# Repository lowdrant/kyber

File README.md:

# kyber
The toy lightsaber I always wanted as a kid.

## Status
* KyberBoard Rev 1 sent out for fabrication.
* Found Luke Skywalker lightsaber CAD for 3D printing by [CaseStudyno8](https://www.thingiverse.com/thing:1263192/files).
* Circuit design complete and subcircuit interfaces frozen.
* Subcircuits passed breadboard feasibility tests.
* First pass on firmware architecture complete.

## Goals
- Build a lightsaber that extends/retracts, lights up, and makes sound
- Demonstrate "full-stack" electronics engineering skills + some mechanical design
- Stay sane for the rest of the pandemic (everyone needs a hobby)
- Maybe have a Luke Skywalker costume by Halloween 2021?

## [fw](fw/)
Written for the [STM32L051K8T6](hw/KyberBoard/symbol-datasheets/stm32l051t8.pdf) microcontroller. Code should work on any STM32 micrcontroller, and most interfaces are abstracted into header files.

TODO: state diagram

### Configuring STM32CubeIde
Edit project settings to include the multi-project libraries and make the compiler optimize for size. TODO: change saber-libs to holocron-libs

## [hw](hw/)
A mildly overdesigned PCB to allow flexibility in mechanical design. Designed for test, assembly, and reconfigurability.

### Component Selection Rules
Keep It Simple, Stupid. Stick to driving circuits that have readily available and easily solderable components. If necessary, target components that have in-stock evaluation boards and take the scrap.

### Current (A) Budget
|Component  |Amperage  |Reasoning                        |
|-----------|----------|---------------------------------|
|motor      |10A       |stall current of on-hand dc motor|
|solenoid   |1A        |12 V/13 Ohms rounded up          |
|3V3 bus    |1A        |typical LDO rating               |
|waste      |0.5A      |safety factor                    |
|-----------|----------|---------------------------------|
|total      |12.5A     |                                 |

### Voltage Loss Budget
Mostly concerned with battery protection I<sup>2</sup>R losses. Target < 0.5V peak drop (instinctive spec, not computed)

Major concerns are
- falling below the solenoid turn-on voltage, although I haven't _really_ settled on a solenoid
- throwing off motor control

Current resolution: use ST's [VNHD7008AY eval board example design](reference-manuals/en-vnhd7008ay.pdf). It seems to work fairly well

### Subcircuits
#### Reverse Polarity Protection
Use the built-in protection of the hbridge. Need to characterise I<sup>2</sup>R losses. This will help prevent the Big Dumb<sup>TM</sup> since I plan to use terminal blocks for my main connector.
#### Low-Voltage Shutoff
Grocery store batteries can't drive the actuators, so I'm looking at using a LiPo. This simple Zener-NMOS-PMOS circuit I designed for a student club will should prevent battery over-discharge.

When the voltage is above Vthresh, the Zener conducts, so the NMOS conducts, which makes the PMOS conduct.
#### 3V3 Bus
LDO; I do not want to deal with buck converters. I am not being paid for this design.
#### Accelerometer/Gyro
For that sweet, sweet _zwoom_. Use I2C/SPI to make routing a little easier. I have a still-in-stock breakout board for the no-longer-produced [MMA84252QT](https://www.digikey.com/catalog/en/partgroup/mma8452q/11242).
#### Motor Current Sensing
I may use torque control to retract the saber. Currently planning to extend it with a spring, so the "retracted torque" is theoretically better characterized than the "retracted position".
#### HBridge
I found a high-current hbridge IC that does not require complementary PWM (thank you ST). I have limited PWM capabilities due to only low-power ST micros being in stock.
#### Actuators
Low-side switches that do not require inrush-limiting resistors to reduce component count. The [SSM3K337R,LF](https://www.digikey.com/en/products/detail/toshiba-semiconductor-and-storage/SSM3K337R-LF/5056502?s=N4IgTCBcDaIMpwLIGYDSzkHYBKIC6AvkA) stays well under the maximum drive current and well-preserves a 20kHz square wave.

### Non-electrical considerations
- Cost: 4 layers. 2-sided board gives me the needed density, and routing isn't that awful
- I'm not sure I want to hand-solder QFN packages
- Size: Maximize density to maximize mechanical design flexibility.
- Power budget: Meh, I can increase resistances after fab if it's a battery killer

## [cad](cad/)
Found a Luke Skywalker lightsaber CAD for 3D printing by [CaseStudyno8](https://www.thingiverse.com/thing:1263192/files). Was also pointed to Disney's [new lightsaber](https://mashable.com/article/real-lightsaber-star-wars-hotel-disney-world/), which shows some novel mechanical design for retraction. Although I would prefer to be able to fence with my design, the tape measure strategy does show promise.

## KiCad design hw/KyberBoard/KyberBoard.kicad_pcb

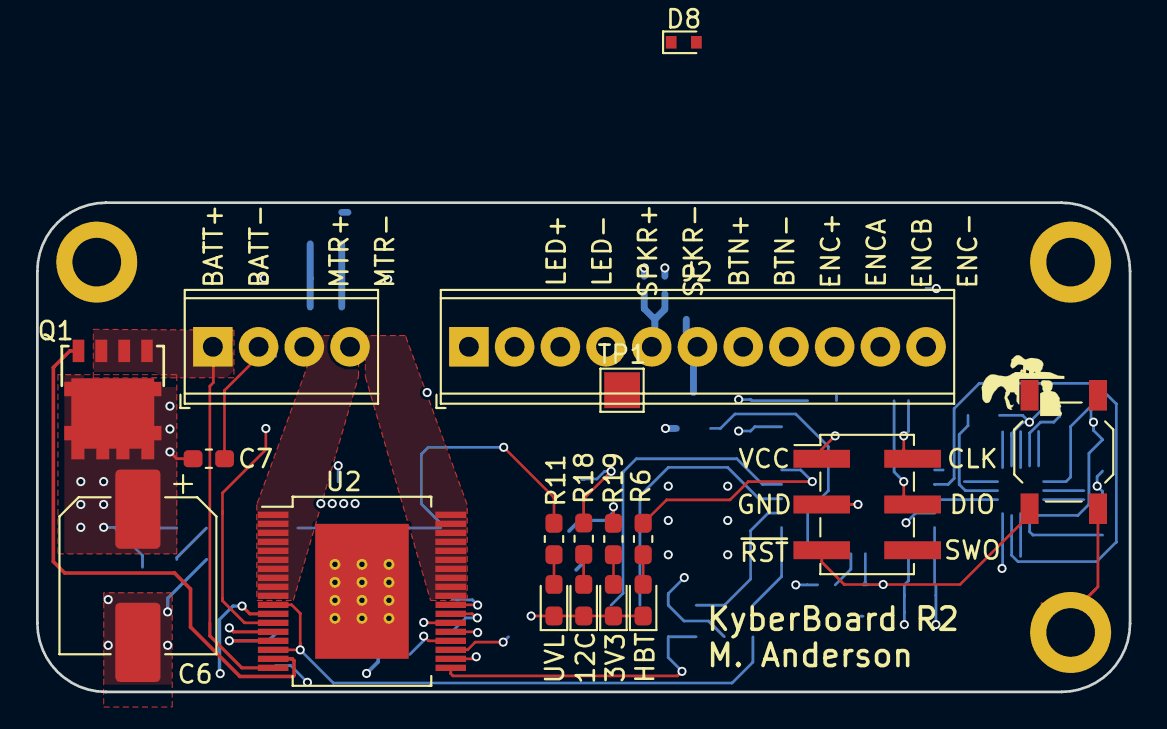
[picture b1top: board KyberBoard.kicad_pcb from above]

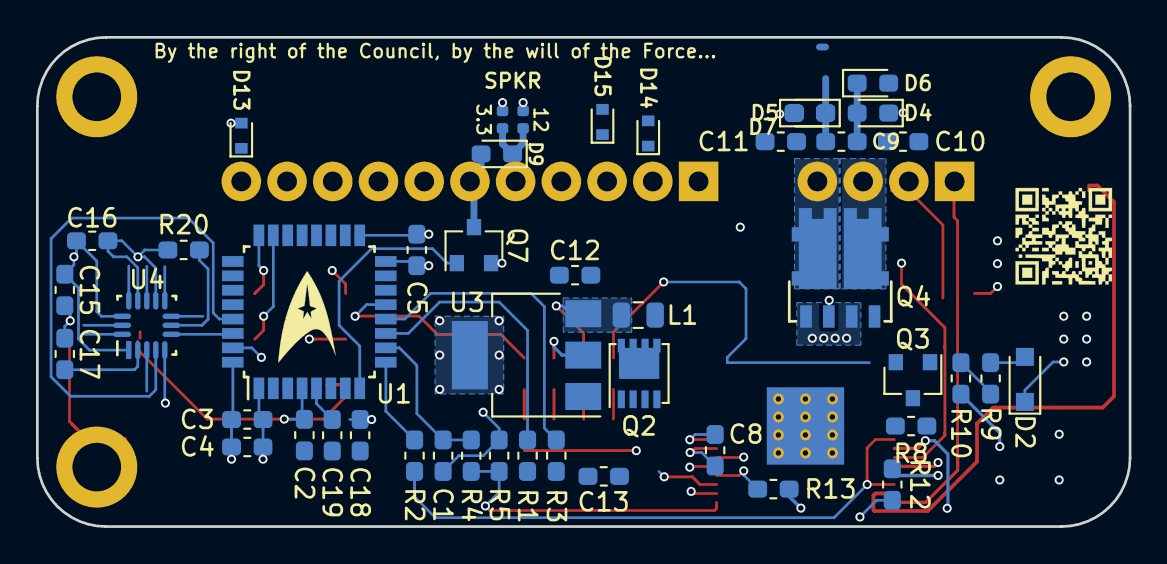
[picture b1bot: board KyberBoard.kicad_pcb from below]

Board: 4 copper layers, 60.7 x 27.2 mm, 67 parts (46 on the bottom side), 44 nets.

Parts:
C1: 33n; C_0603_1608Metric_Pad1.05x0.95mm_HandSolder
C2, C4, C5, C7, C8, C15, C17, C18: 100n; C_0603_1608Metric_Pad1.05x0.95mm_HandSolder
C3, C12: 10u; C_0603_1608Metric_Pad1.05x0.95mm_HandSolder
C6: 200u; CP_Elec_8x10.5
C9, C10, C11: 10n; C_0603_1608Metric_Pad1.05x0.95mm_HandSolder
C13: 22u; C_0603_1608Metric_Pad1.05x0.95mm_HandSolder
C16: 4u7; C_0603_1608Metric_Pad1.05x0.95mm_HandSolder
C19: 1u; C_0603_1608Metric_Pad1.05x0.95mm_HandSolder
D1: 150060VS75020; LED_0603_1608Metric_Pad1.05x0.95mm_HandSolder
D2: BZT52C8V2S-7-F; D_SOD-323_HandSoldering
D3: 150060RS75020; LED_0603_1608Metric_Pad1.05x0.95mm_HandSolder
D4, D5, D6, D7, D9: SDM2U30CSP-7; D_0603_1608Metric_Pad1.05x0.95mm_HandSolder
D8, D13, D14, D15: BZT585B3V6T; D_SOD-523
D10, D11: 150060AS75000; LED_0603_1608Metric_Pad1.05x0.95mm_HandSolder
H1, H3, H4: MountingHole_Pad; MountingHole_2.7mm_M2.5_ISO7380_Pad
J1: Screw_Terminal_01x04; TerminalBlock_Phoenix_MPT-0,5-4-2.54_1x04_P2.54mm_Horizontal
J2: Screw_Terminal_01x11; TerminalBlock_Phoenix_MPT-0,5-11-2.54_1x11_P2.54mm_Horizont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
J4: 15910060; PinHeader_2x03_P2.54mm_Vertical_SMD
L1: CIGT201210UHR47MNE; C_0805_2012Metric
Q1: STL120N4F6AG
Q2: SIS413DN-T1-GE3; Vishay_PowerPAK_1212-8_Single
Q3: SSM3K337R; SOT-23
Q4: STL76DN4LF7AG
Q7: SSM3K337R,LF; SOT-23
R1, R2, R3, R6, R8, R10, R19, R20: 1k; R_0603_1608Metric_Pad1.05x0.95mm_HandSolder
R4, R11, R12, R13, R18: 10k; R_0603_1608Metric_Pad1.05x0.95mm_HandSolder
R5: 1k5; R_0603_1608Metric_Pad1.05x0.95mm_HandSolder
R9: 0; R_0603_1608Metric_Pad1.05x0.95mm_HandSolder
R16, R17: 0; R_0402_1005Metric
SW1: TL3342F160QG/TR; SW_SPST_TL3342
TP1: TestPoint; TestPoint_Pad_2.0x2.0mm
U1: STM32L051K8T6; LQFP-32_7x7mm_P0.8mm
U2: VNHD7008AY; ST_PowerSSO-36_SlugDown_ThermalVias
U3: AZ1117IH-3.3TRG1; SOT-223-3_TabPin2
U4: MMA8452QT; MMA8452Q

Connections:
+3V3: C3.1, C4.1, C5.1, C13.1, C15.2, C16.2, C18.1, C19.1, J2.1, J2.7, J2.10, J4.1, R17.1, R19.1, U1.1, U1.5, U1.17, U2.12, U3.2, U4.1, U4.14
+12C: C12.2, L1.1, R18.1, U3.3
+12V: L1.2, Q2.5, R16.2
/BATT+: J1.1, Q1.1, Q1.2, Q1.3, U2.18
/BTN: D13.1, J2.11, U1.19
/ENC_A: D14.1, J2.2, U1.28
/ENC_B: D15.1, J2.3, U1.27
/LED_TX: D8.1, J2.8
/MOT+: C9.2, C10.1, D4.2, D6.1, J1.3, Q4.5/6, U2.1, U2.2, U2.3, U2.4, U2.5, U2.6, U2.7, U2.8, U2.9, U2.10
/MOT-: C9.1, C11.1, D5.2, D7.1, J1.4, Q4.7/8, U2.27, U2.28, U2.29, U2.30, U2.31, U2.32, U2.33, U2.34, U2.35, U2.36
/SPKR+: D9.1, J2.5, R16.1, R17.2
/SPKR-: D9.2, J2.6, Q7.3
/V_UNSAFE: C6.1, C7.1, D2.1, D4.1, D5.1, Q1.5, Q2.1, Q2.2, Q2.3, R8.1, U2.37
/acc/SCL: U1.29, U4.4
/acc/SDA: U1.30, U4.6
/actuators/PWM_SPKR: Q7.1, TP1.1, U1.8
/hbridge/INA: R2.2, U2.11, U2.16
/hbridge/INB: R3.2, U2.21
/hbridge/PWM_MTR: R1.2, U2.20
/hbridge/imtr: R4.2, R5.1, U2.19
/micro/ADC_imtr: C1.1, R4.1, U1.10
/micro/INA_MCU: R2.1, U1.9
/micro/INB_MCU: R3.1, U1.12
/micro/LED_HBEAT: R6.2, U1.13
/micro/NRST: C2.1, J4.5, SW1.1, U1.4
/micro/PWM_MTR_MCU: R1.1, U1.11
/micro/SWCLK: J4.2, U1.24
/micro/SWDIO: J4.4, U1.23
GND: C1.2, C2.2, C3.2, C4.2, C5.2, C6.2, C7.2, C8.2, C10.2, C11.2, C12.1, C13.2, C15.1, C16.1, C17.1, C18.2, C19.2, D1.1, D3.1, D6.2, D7.2, D8.2, D10.1, D11.1, D13.2, D14.2, D15.2, H1.1, H3.1, H4.1, J1.2, J2.4, J2.9, J4.3, Q3.2, Q4.1, Q4.3, Q7.2, R5.2, R10.1, R12.2, R13.2, R20.2, SW1.2, U1.16, U1.31, U1.32, U2.14, U2.23, U2.26, U3.1, U4.5, U4.10, U4.12
unnamed: C8.1, U2.25
unnamed: C17.2, U4.2
unnamed: D1.2, R6.1
unnamed: D2.2, R9.2
unnamed: D3.2, R11.2
unnamed: D10.2, R18.2
unnamed: D11.2, R19.2
unnamed: Q1.4, U2.17
unnamed: Q2.4, Q3.3, R8.2, R11.1
unnamed: Q3.1, R9.1, R10.2
unnamed: Q4.2, U2.24
unnamed: Q4.4, U2.13
unnamed: R12.1, U2.15
unnamed: R13.1, U2.22
unnamed: R20.1, U4.7

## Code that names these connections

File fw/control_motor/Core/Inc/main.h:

/* USER CODE BEGIN Header */
/**
  ******************************************************************************
  * @file           : main.h
  * @brief          : Header for main.c file.
  *                   This file contains the common defines of the application.
  ******************************************************************************
  * @attention
  *
  * <h2><center>&copy; Copyright (c) 2021 STMicroelectronics.
  * All rights reserved.</center></h2>
  *
  * This software component is licensed by ST under BSD 3-Clause license,
  * the "License"; You may not use this file except in compliance with the
  * License. You may obtain a copy of the License at:
  *                        opensource.org/licenses/BSD-3-Clause
  *
  ******************************************************************************
  */
/* USER CODE END Header */

/* Define to prevent recursive inclusion -------------------------------------*/
#ifndef __MAIN_H
#define __MAIN_H

#ifdef __cplusplus
extern "C" {
#endif

/* Includes ------------------------------------------------------------------*/
#include "stm32l0xx_hal.h"

/* Private includes ----------------------------------------------------------*/
/* USER CODE BEGIN Includes */
/* USER CODE END Includes */

/* Exported types ------------------------------------------------------------*/
/* USER CODE BEGIN ET */

/* USER CODE END ET */

/* Exported constants --------------------------------------------------------*/
/* USER CODE BEGIN EC */
#define T_HBEAT (float) 0.5  // LED Heartbeat Period
#define T_MTR (float) 0.1    // mot stuff
/* USER CODE END EC */

/* Exported macro ------------------------------------------------------------*/
/* USER CODE BEGIN EM */

/* USER CODE END EM */

void HAL_TIM_MspPostInit(TIM_HandleTypeDef *htim);

/* Exported functions prototypes ---------------------------------------------*/
void Error_Handler(void);

/* USER CODE BEGIN EFP */

/* USER CODE END EFP */

/* Private defines -----------------------------------------------------------*/
#define SIG_LED_Pin GPIO_PIN_14
#define SIG_LED_GPIO_Port GPIOC
#define SIG_SOL_Pin GPIO_PIN_15
#define SIG_SOL_GPIO_Port GPIOC
#define PWM_SPKR_Pin GPIO_PIN_0
#define PWM_SPKR_GPIO_Port GPIOA
#define PWM_MTR_Pin GPIO_PIN_1
#define PWM_MTR_GPIO_Port GPIOA
#define INA_Pin GPIO_PIN_2
#define INA_GPIO_Port GPIOA
#define INB_Pin GPIO_PIN_3
#define INB_GPIO_Port GPIOA
#define ADC_imtr_Pin GPIO_PIN_4
#define ADC_imtr_GPIO_Port GPIOA
#define LED_HBEAT_Pin GPIO_PIN_5
#define LED_HBEAT_GPIO_Port GPIOA
#define ENC_B_Pin GPIO_PIN_6
#define ENC_B_GPIO_Port GPIOA
#define ENC_A_Pin GPIO_PIN_7
#define ENC_A_GPIO_Port GPIOA
#define BTN_Pin GPIO_PIN_1
#define BTN_GPIO_Port GPIOB
#define BTN_EXTI_IRQn EXTI0_1_IRQn
/* USER CODE BEGIN Private defines */

/* USER CODE END Private defines */

#ifdef __cplusplus
}
#endif

#endif /* __MAIN_H */

/************************ (C) COPYRIGHT STMicroelectronics *****END OF FILE****/

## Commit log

2021-04-07 firmware setup & gitignore
2021-04-07 Ticks-based scheduler & heartbeat. Update gitignore
2021-04-07 Basic scheduler, additional hardward considerations
2021-04-07 Switched to STM32G031F8P6 chip for more flash memory
2021-04-07 exploring spi hbridge options
2021-04-07 testing switch to STM32L031F4
2021-04-07 basic code that compiles. fighting with cubemx
2021-04-07 Use CubeIDE-1.3.0. Working blinky/accelermeter I2C.
2021-04-07 initial hbridge/fet sims
2021-04-07 starting gpio interrupt configuration
2021-04-07 motor parameter spreadsheet
2021-04-07 GPIO interrupts and better state machine. Cleaner code
2021-04-07 ltspice gitignore/cleanup
2021-04-23 sim files & pdfs
2021-04-24 init PCB schematic - hierarchy,mcu pinout,some chip selection,basic circuit implementation
2021-04-24 Create LICENSE
2021-04-24 Add hw documentation to README
2021-04-24 sized battery protections FETs,zeners,resistors
2021-04-24 forgot to push pcb .lib file :(
2021-04-24 saving partially complete hbridge symbol just in case
2021-04-24 working on actuators. some schematic cleanup
2021-04-24 adding hierarchy to LTSpice
2021-04-24 redid sch to use hbridge IC significant built-in functionality
2021-04-24 update rpp circuit description in readme
2021-04-25 major schematic cleanup. sized diodes.
2021-04-25 minor schematic formatting
2021-05-02 ERC cleanup; sized capacitors and inductors
2021-05-02 found mosfet with denser footprint. search now renewed
2021-05-02 ditched battery sensing & chose basic footprints
2021-05-02 repicked mcu pins for layout
2021-05-02 better hierarchy; more footprint assignment
2021-05-06 started motor control code. needs serious readability architecture
2021-05-06 moving to multiple fw 'projects' for testing & characterization
2021-05-06 working on motor characterization project, updated readme
2021-05-06 working chan2 pwm -- pulse_chan/counter_period = duty cycle
2021-05-07 working motor duty cycle & dir control
2021-05-07 pwm sweep demo
2021-05-08 working encoder
2021-05-08 avoid encoder double/quadruple counting by bitshifting - (TIM22->CNT)>>1
2021-05-08 signed encoder working (use int16)
2021-05-08 Characterization interface initially complete
2021-05-08 started motor control subproj
2021-05-09 Ready-for-first-layout schematic.
    TODOs
    - correct power fet footprints
    - pick similar ST micro (need more flash for floats)
2021-05-09 building motor control testing
2021-05-09 accelerometer pinout correction
2021-05-09 reselected diodes, split up connector TBs for layout purposes
2021-05-13 started cad for winding winch
2021-05-13 rechose diodes for density
2021-05-14 pre-datasheet-review placement
2021-05-14 4 layer board for density. Need to re-choose motor cap
2021-05-14 additional layout changes for density
2021-05-14 increased density by removing a mounting hole so large cap takes up that corner
2021-05-16 base saber stls from thingiverse (see credits.txt)
2021-05-21 editing layout for density
2021-05-21 more shrinking layout
2021-05-22 Maximum density placement. Next: Tidy for routing + minor footprint corrections
2021-05-26 correct weird pad for STL76DN4LF7AG
2021-05-26 STL76DN4LF7AG both weird pads dimensioned correctly
2021-05-26 STL76DN4LF7AG weird pads now pads
2021-05-26 STL76DN4LF7AG footprint updated
2021-05-26 pre-netlist reload commit. st transistor updated symbols + footprints
2021-05-27 power+hbridge routing round 1. fixed a transistor orientation error.
2021-05-29 starting signal routing
2021-05-29 noted more pin-specific capacitor connections
2021-05-29 removed all testpoints for density reasons. may add SDA/SCL test points back in
2021-05-29 Initial routing complete
2021-05-29 renamed PCB project to KyberBoard
2021-05-29 moved to L051K8 mcu. renamed project from 'saber' to 'holocron'
2021-05-29 forgot to change project name in readme
2021-06-01 finally pushed project symbol lib file
2021-06-04 working adc code and minor circuit correction
2021-06-06 prepping board for fab -- DRC,easter eggs,silkscreen
2021-06-06 corrected FET footprint (missing mask on pad) and more easter eggs
2021-06-07 cleaned silkscreen and checked design rules. almost ready for fab
2021-06-07 board ready to send out to fab
2021-06-07 found major ACC footprint error. Corrected + redid local placement + routing
2021-06-07 gerber files updated per JLCPCB Kicad5 tutorial
2021-06-08 Completed BOM; board sent to fab house
2021-06-08 drawing cleanup & pdfs
2021-06-10 documentation updates
2021-07-04 PCB Bring-Up Day 1 Revisions
    - Touched up undervoltage cutout circuit
    - Stronger PMOS pull-up (10kOhms was not working; replaced with 1k & called good)
    - 10kOhms LED current-limiting resistor
    - Corrected minor schematic discrepancies from PCB
    - undervoltage indicator circuit was correct in PCB but not schematic
    - Changed mounting holes from M3 to M2.5 (Raspberry Pi size)
2021-07-05 timer-interrupt heartbeat. working on button + motor control
2021-07-06 working encoder code in holocron
2021-07-06 basic control loop implementation
2021-07-08 control cleanup and speaker freq implementation
2021-08-01 starting saber chassis testbed
2021-08-28 started work on winch system
2021-08-31 reworking pcb to be compatible with LED strip
